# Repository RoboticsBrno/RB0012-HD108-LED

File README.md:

# HD108 LEDs

We all love addressable LEDs such as WS2812B. But they suffer from two problems:
- they have high current consumption in the off state – about 1 mA.
- It's nice to have a single-wire protocol for driving these LEDs. However
  generating this signal is not often that easy on common microcontrollers.
  Also, there are many flavours out there that differ in the timing
  requirements.
- They have no gamma correction and only 8-bit PWM.

There seem to be a new kind of LED -
[HD108](https://www.rose-lighting.com/wp-content/uploads/sites/53/2022/07/HD108-Specificaion-V1.2.pdf)
that:
- uses traditional SPI,
- has 16-bit PWM + 5-bit brightness control so gamma correction is actually
  possible.
- claims to have 1 µA power consumption when off.

This repository contains PCB & software to test these LEDs.

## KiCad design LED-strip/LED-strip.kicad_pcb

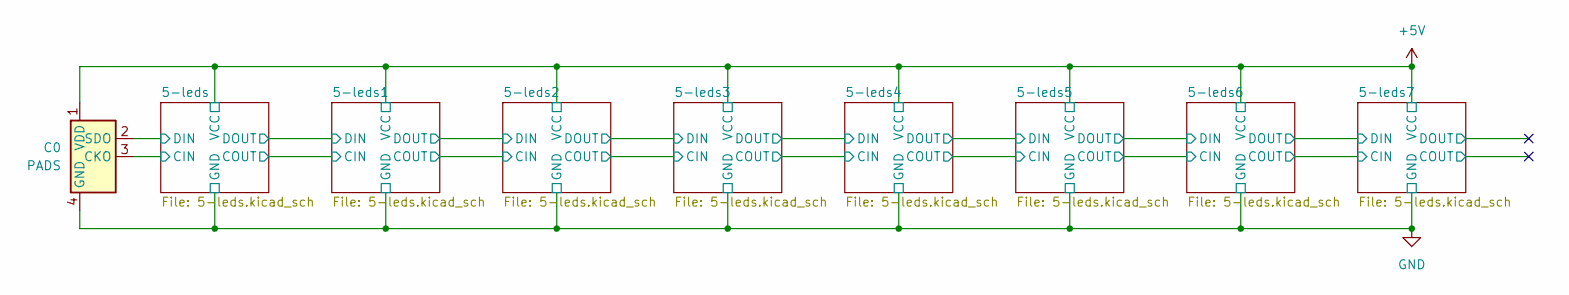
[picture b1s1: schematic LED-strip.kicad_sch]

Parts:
C0: PADS; LED-pads

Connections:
+5V: C0.1 (VDD); also elsewhere on the board
/5-leds/CIN: C0.3 (CKO); also elsewhere on the board
/5-leds/DIN: C0.2 (SDO); also elsewhere on the board
GND: C0.4 (GND); also elsewhere on the board

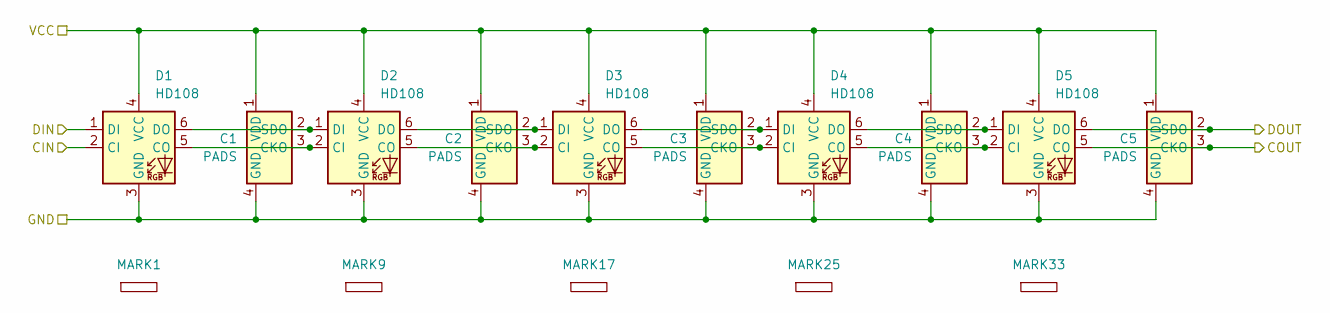
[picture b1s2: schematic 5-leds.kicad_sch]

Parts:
C1, C2, C3, C4, C5: PADS; LED-pads
D1, D2, D3, D4, D5: HD108; LED_RGB_5050-6
MARK1, MARK9, MARK17, MARK25, MARK33: LED_STRIP_MARKING

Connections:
+5V: C1.1 (VDD), C2.1 (VDD), C3.1 (VDD), C4.1 (VDD), C5.1 (VDD), D1.4 (VCC), D2.4 (VCC), D3.4 (VCC), D4.4 (VCC), D5.4 (VCC); also elsewhere on the board
/5-leds/CIN: D1.2 (CI); also elsewhere on the board
/5-leds/COUT: C5.3 (CKO), D5.5 (CO); also elsewhere on the board
/5-leds/DIN: D1.1 (DI); also elsewhere on the board
/5-leds/DOUT: C5.2 (SDO), D5.6 (DO); also elsewhere on the board
GND: C1.4 (GND), C2.4 (GND), C3.4 (GND), C4.4 (GND), C5.4 (GND), D1.3 (GND), D2.3 (GND), D3.3 (GND), D4.3 (GND), D5.3 (GND); also elsewhere on the board
unnamed: C1.3 (CKO), D1.5 (CO), D2.2 (CI)
unnamed: C1.2 (SDO), D1.6 (DO), D2.1 (DI)
unnamed: C2.3 (CKO), D2.5 (CO), D3.2 (CI)
unnamed: C2.2 (SDO), D2.6 (DO), D3.1 (DI)
unnamed: C3.3 (CKO), D3.5 (CO), D4.2 (CI)
unnamed: C3.2 (SDO), D3.6 (DO), D4.1 (DI)
unnamed: C4.3 (CKO), D4.5 (CO), D5.2 (CI)
unnamed: C4.2 (SDO), D4.6 (DO), D5.1 (DI)

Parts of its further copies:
C6, C7, C8, C9, C10, C11, C12, C13, C14, C15, C16, C17, C18, C19, C20, C21, C22, C23, C24, C25, C26, C27, C28, C29, C30, C31, C32, C33, C34, C35, C36, C37, C38, C39, C40: PADS; LED-pads
D6, D7, D8, D9, D10, D11, D12, D13, D14, D15, D16, D17, D18, D19, D20, D21, D22, D23, D24, D25, D26, D27, D28, D29, D30, D31, D32, D33, D34, D35, D36, D37, D38, D39, D40: HD108; LED_RGB_5050-6
MARK2, MARK3, MARK4, MARK5, MARK6, MARK7, MARK8, MARK10, MARK11, MARK12, MARK13, MARK14, MARK15, MARK16, MARK18, MARK19, MARK20, MARK21, MARK22, MARK23, MARK24, MARK26, MARK27, MARK28, MARK29, MARK30, MARK31, MARK32, MARK34, MARK35, MARK36, MARK37, MARK38, MARK39, MARK40: LED_STRIP_MARKING

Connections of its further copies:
+5V: C6.1 (VDD), C7.1 (VDD), C8.1 (VDD), C9.1 (VDD), C10.1 (VDD), C11.1 (VDD), C12.1 (VDD), C13.1 (VDD), C14.1 (VDD), C15.1 (VDD), C16.1 (VDD), C17.1 (VDD), C18.1 (VDD), C19.1 (VDD), C20.1 (VDD), C21.1 (VDD), C22.1 (VDD), C23.1 (VDD), C24.1 (VDD), C25.1 (VDD), C26.1 (VDD), C27.1 (VDD), C28.1 (VDD), C29.1 (VDD), C30.1 (VDD), C31.1 (VDD), C32.1 (VDD), C33.1 (VDD), C34.1 (VDD), C35.1 (VDD), C36.1 (VDD), C37.1 (VDD), C38.1 (VDD), C39.1 (VDD), C40.1 (VDD), D6.4 (VCC), D7.4 (VCC), D8.4 (VCC), D9.4 (VCC), D10.4 (VCC), D11.4 (VCC), D12.4 (VCC), D13.4 (VCC), D14.4 (VCC), D15.4 (VCC), D16.4 (VCC), D17.4 (VCC), D18.4 (VCC), D19.4 (VCC), D20.4 (VCC), D21.4 (VCC), D22.4 (VCC), D23.4 (VCC), D24.4 (VCC), D25.4 (VCC), D26.4 (VCC), D27.4 (VCC), D28.4 (VCC), D29.4 (VCC), D30.4 (VCC), D31.4 (VCC), D32.4 (VCC), D33.4 (VCC), D34.4 (VCC), D35.4 (VCC), D36.4 (VCC), D37.4 (VCC), D38.4 (VCC), D39.4 (VCC), D40.4 (VCC); also elsewhere on the board
/5-leds1/COUT: C10.3 (CKO), D10.5 (CO), D11.2 (CI)
/5-leds1/DOUT: C10.2 (SDO), D10.6 (DO), D11.1 (DI)
/5-leds2/COUT: C15.3 (CKO), D15.5 (CO), D16.2 (CI)
/5-leds2/DOUT: C15.2 (SDO), D15.6 (DO), D16.1 (DI)
/5-leds3/COUT: C20.3 (CKO), D20.5 (CO), D21.2 (CI)
/5-leds3/DOUT: C20.2 (SDO), D20.6 (DO), D21.1 (DI)
/5-leds4/COUT: C25.3 (CKO), D25.5 (CO), D26.2 (CI)
/5-leds4/DOUT: C25.2 (SDO), D25.6 (DO), D26.1 (DI)
/5-leds5/COUT: C30.3 (CKO), D30.5 (CO), D31.2 (CI)
/5-leds5/DOUT: C30.2 (SDO), D30.6 (DO), D31.1 (DI)
/5-leds6/COUT: C35.3 (CKO), D35.5 (CO), D36.2 (CI)
/5-leds6/DOUT: C35.2 (SDO), D35.6 (DO), D36.1 (DI)
/5-leds7/COUT: C40.3 (CKO), D40.5 (CO)
/5-leds7/DOUT: C40.2 (SDO), D40.6 (DO)
/5-leds/COUT: D6.2 (CI); also elsewhere on the board
/5-leds/DOUT: D6.1 (DI); also elsewhere on the board
GND: C6.4 (GND), C7.4 (GND), C8.4 (GND), C9.4 (GND), C10.4 (GND), C11.4 (GND), C12.4 (GND), C13.4 (GND), C14.4 (GND), C15.4 (GND), C16.4 (GND), C17.4 (GND), C18.4 (GND), C19.4 (GND), C20.4 (GND), C21.4 (GND), C22.4 (GND), C23.4 (GND), C24.4 (GND), C25.4 (GND), C26.4 (GND), C27.4 (GND), C28.4 (GND), C29.4 (GND), C30.4 (GND), C31.4 (GND), C32.4 (GND), C33.4 (GND), C34.4 (GND), C35.4 (GND), C36.4 (GND), C37.4 (GND), C38.4 (GND), C39.4 (GND), C40.4 (GND), D6.3 (GND), D7.3 (GND), D8.3 (GND), D9.3 (GND), D10.3 (GND), D11.3 (GND), D12.3 (GND), D13.3 (GND), D14.3 (GND), D15.3 (GND), D16.3 (GND), D17.3 (GND), D18.3 (GND), D19.3 (GND), D20.3 (GND), D21.3 (GND), D22.3 (GND), D23.3 (GND), D24.3 (GND), D25.3 (GND), D26.3 (GND), D27.3 (GND), D28.3 (GND), D29.3 (GND), D30.3 (GND), D31.3 (GND), D32.3 (GND), D33.3 (GND), D34.3 (GND), D35.3 (GND), D36.3 (GND), D37.3 (GND), D38.3 (GND), D39.3 (GND), D40.3 (GND); also elsewhere on the board
unnamed: C6.3 (CKO), D6.5 (CO), D7.2 (CI)
unnamed: C6.2 (SDO), D6.6 (DO), D7.1 (DI)
unnamed: C7.3 (CKO), D7.5 (CO), D8.2 (CI)
unnamed: C7.2 (SDO), D7.6 (DO), D8.1 (DI)
unnamed: C8.3 (CKO), D8.5 (CO), D9.2 (CI)
unnamed: C8.2 (SDO), D8.6 (DO), D9.1 (DI)
unnamed: C9.3 (CKO), D9.5 (CO), D10.2 (CI)
unnamed: C9.2 (SDO), D9.6 (DO), D10.1 (DI)
unnamed: C11.3 (CKO), D11.5 (CO), D12.2 (CI)
unnamed: C11.2 (SDO), D11.6 (DO), D12.1 (DI)
unnamed: C12.3 (CKO), D12.5 (CO), D13.2 (CI)
unnamed: C12.2 (SDO), D12.6 (DO), D13.1 (DI)
unnamed: C13.3 (CKO), D13.5 (CO), D14.2 (CI)
unnamed: C13.2 (SDO), D13.6 (DO), D14.1 (DI)
unnamed: C14.3 (CKO), D14.5 (CO), D15.2 (CI)
unnamed: C14.2 (SDO), D14.6 (DO), D15.1 (DI)
unnamed: C16.3 (CKO), D16.5 (CO), D17.2 (CI)
unnamed: C16.2 (SDO), D16.6 (DO), D17.1 (DI)
unnamed: C17.3 (CKO), D17.5 (CO), D18.2 (CI)
unnamed: C17.2 (SDO), D17.6 (DO), D18.1 (DI)
unnamed: C18.3 (CKO), D18.5 (CO), D19.2 (CI)
unnamed: C18.2 (SDO), D18.6 (DO), D19.1 (DI)
unnamed: C19.3 (CKO), D19.5 (CO), D20.2 (CI)
unnamed: C19.2 (SDO), D19.6 (DO), D20.1 (DI)
unnamed: C21.3 (CKO), D21.5 (CO), D22.2 (CI)
unnamed: C21.2 (SDO), D21.6 (DO), D22.1 (DI)
unnamed: C22.3 (CKO), D22.5 (CO), D23.2 (CI)
unnamed: C22.2 (SDO), D22.6 (DO), D23.1 (DI)
unnamed: C23.3 (CKO), D23.5 (CO), D24.2 (CI)
unnamed: C23.2 (SDO), D23.6 (DO), D24.1 (DI)
unnamed: C24.3 (CKO), D24.5 (CO), D25.2 (CI)
unnamed: C24.2 (SDO), D24.6 (DO), D25.1 (DI)
unnamed: C26.3 (CKO), D26.5 (CO), D27.2 (CI)
unnamed: C26.2 (SDO), D26.6 (DO), D27.1 (DI)
unnamed: C27.3 (CKO), D27.5 (CO), D28.2 (CI)
unnamed: C27.2 (SDO), D27.6 (DO), D28.1 (DI)
unnamed: C28.3 (CKO), D28.5 (CO), D29.2 (CI)
unnamed: C28.2 (SDO), D28.6 (DO), D29.1 (DI)
unnamed: C29.3 (CKO), D29.5 (CO), D30.2 (CI)
unnamed: C29.2 (SDO), D29.6 (DO), D30.1 (DI)
unnamed: C31.3 (CKO), D31.5 (CO), D32.2 (CI)
unnamed: C31.2 (SDO), D31.6 (DO), D32.1 (DI)
unnamed: C32.3 (CKO), D32.5 (CO), D33.2 (CI)
unnamed: C32.2 (SDO), D32.6 (DO), D33.1 (DI)
unnamed: C33.3 (CKO), D33.5 (CO), D34.2 (CI)
unnamed: C33.2 (SDO), D33.6 (DO), D34.1 (DI)
unnamed: C34.3 (CKO), D34.5 (CO), D35.2 (CI)
unnamed: C34.2 (SDO), D34.6 (DO), D35.1 (DI)
unnamed: C36.3 (CKO), D36.5 (CO), D37.2 (CI)
unnamed: C36.2 (SDO), D36.6 (DO), D37.1 (DI)
unnamed: C37.3 (CKO), D37.5 (CO), D38.2 (CI)
unnamed: C37.2 (SDO), D37.6 (DO), D38.1 (DI)
unnamed: C38.3 (CKO), D38.5 (CO), D39.2 (CI)
unnamed: C38.2 (SDO), D38.6 (DO), D39.1 (DI)
unnamed: C39.3 (CKO), D39.5 (CO), D40.2 (CI)
unnamed: C39.2 (SDO), D39.6 (DO), D40.1 (DI)

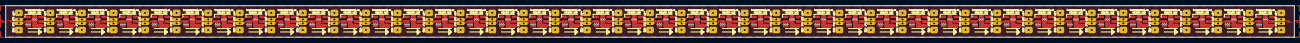
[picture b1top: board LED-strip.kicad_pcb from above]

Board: 2 copper layers, 490.0 x 12.0 mm, 121 parts (0 on the bottom side), 84 nets.
